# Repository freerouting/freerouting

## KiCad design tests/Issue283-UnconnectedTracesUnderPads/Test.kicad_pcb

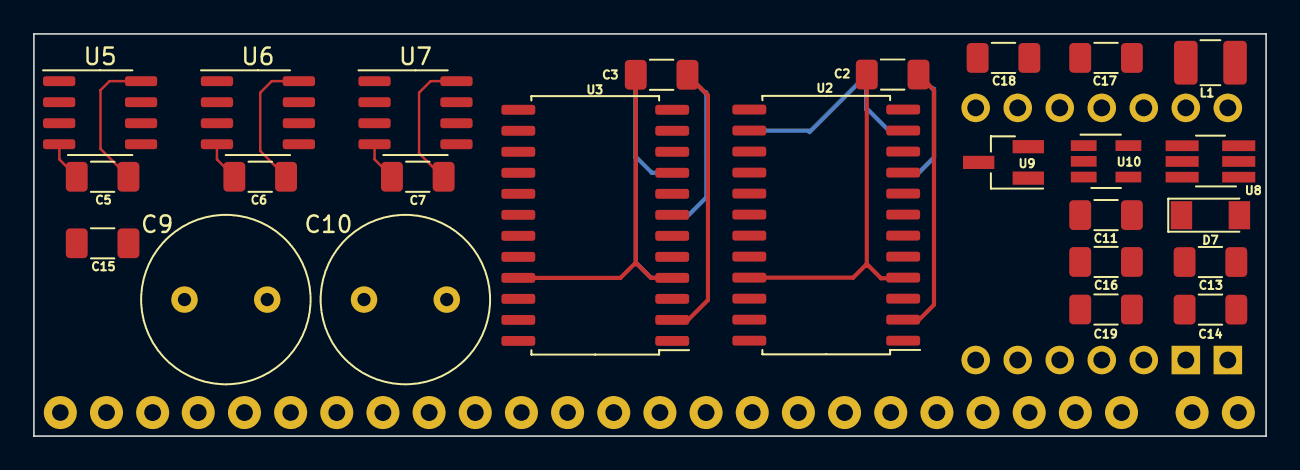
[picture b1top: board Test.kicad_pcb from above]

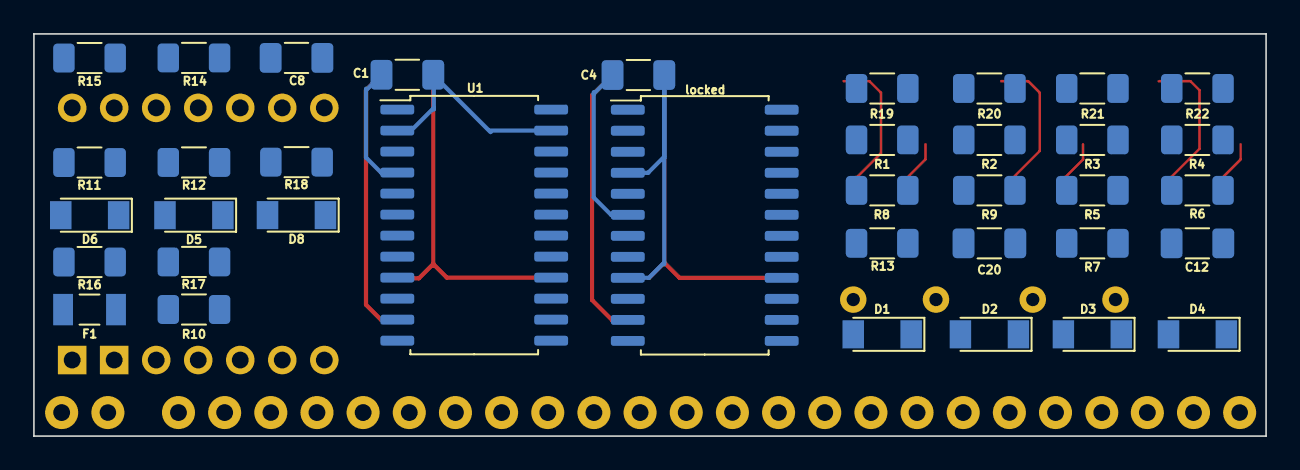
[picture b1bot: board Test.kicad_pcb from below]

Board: 2 copper layers, 74.5 x 24.3 mm, 89 parts (37 on the bottom side), 57 nets.

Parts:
C1, C2, C3, C4, C5, C6, C7, C8, C12, C19: 0.1u; C_1206_3216Metric_Pad1.33x1.80mm_HandSolder
C9, C10: 47u; C_Radial_D10.0mm_H12.5mm_P5.00mm
C11: 10u; C_1206_3216Metric_Pad1.33x1.80mm_HandSolder
C13, C14, C15: 47u; C_1206_3216Metric_Pad1.33x1.80mm_HandSolder
C16, C17, C18, C20: 0.01u; C_1206_3216Metric_Pad1.33x1.80mm_HandSolder
D1, D2, D3, D4, D5, D6, D7, D8: LL4148; D_MiniMELF
F1: 0.1 A; Fuse_Bussman_1206_3216Metric_Pad1.42x1.75mm_HandSolder
J1: 1A+; SolderWirePad_1x01_Drill0.8mm
J2: 1A-; SolderWirePad_1x01_Drill0.8mm
J3: 1B+; SolderWirePad_1x01_Drill0.8mm
J4: 1B-; SolderWirePad_1x01_Drill0.8mm
J5: 2A+; SolderWirePad_1x01_Drill0.8mm
J6: 2A-; SolderWirePad_1x01_Drill0.8mm
J7: 2B+; SolderWirePad_1x01_Drill0.8mm
J8: 2B-; SolderWirePad_1x01_Drill0.8mm
J9: 3A+; SolderWirePad_1x01_Drill0.8mm
J10: 3A-; SolderWirePad_1x01_Drill0.8mm
J11: 3B+; SolderWirePad_1x01_Drill0.8mm
J12: 3B-; SolderWirePad_1x01_Drill0.8mm
J13: POT A; SolderWirePad_1x01_Drill0.8mm
J14: POT B; SolderWirePad_1x01_Drill0.8mm
J15: VOL W; SolderWirePad_1x01_Drill0.8mm
J16: PRE W; SolderWirePad_1x01_Drill0.8mm
J17: MOD W; SolderWirePad_1x01_Drill0.8mm
J18: LED +; SolderWirePad_1x01_Drill0.8mm
J19: LED D; SolderWirePad_1x01_Drill0.8mm
J20: LED -; SolderWirePad_1x01_Drill0.8mm
J21: OUT +; SolderWirePad_1x01_Drill0.8mm
J22: OUT -; SolderWirePad_1x01_Drill0.8mm
J23: OUT G; SolderWirePad_1x01_Drill0.8mm
J24: BAT +; SolderWirePad_1x01_Drill0.8mm
J25: BAT -; SolderWirePad_1x01_Drill0.8mm
J28: GND; SolderWirePad_1x01_Drill0.8mm
L1: 4.7u; L_1210_3225Metric_Pad1.42x2.65mm_HandSolder
R1, R2, R3, R4, R14: 1M; R_1206_3216Metric_Pad1.30x1.75mm_HandSolder
R5, R6: 47k; R_1206_3216Metric_Pad1.30x1.75mm_HandSolder
R7: 10; R_1206_3216Metric_Pad1.30x1.75mm_HandSolder
R8, R9: 100; R_1206_3216Metric_Pad1.30x1.75mm_HandSolder
R10, R13: 1K; R_1206_3216Metric_Pad1.30x1.75mm_HandSolder
R11, R12: 100k; R_1206_3216Metric_Pad1.30x1.75mm_HandSolder
R15: 10M; R_1206_3216Metric_Pad1.30x1.75mm_HandSolder
R16: 300k; R_1206_3216Metric_Pad1.30x1.75mm_HandSolder
R17: 10k; R_1206_3216Metric_Pad1.30x1.75mm_HandSolder
R18: 43k; R_1206_3216Metric_Pad1.30x1.75mm_HandSolder
R19, R20, R21, R22: 4k7; R_1206_3216Metric_Pad1.30x1.75mm_HandSolder
U1, U2, U3: MAX395CWG+; SOIC-24W_7.5x15.4mm_P1.27mm
U5, U6, U7: OPA2314/OPA2205/OPA1692; SOIC-8_3.9x4.9mm_P1.27mm
U8: AP63205WU; TSOT-23-6_HandSoldering
U9: ATL431; SOT-23_Handsoldering
U10: AP7383-44WR-7; SOT-23-5_HandSoldering
U11: SeeeduinoXIAO; Seeeduino_XIAO-MOUDLE14P-2.54-21X17.8MM_PINS
locked: AD5206BRZ50; SOIC-24W_7.5x15.4mm_P1.27mm

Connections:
+5V: C1.1, C2.1, C3.1, C4.1, C5.1, C6.1, C7.1, C13.1, C14.1, D1.1 (K), D2.1 (K), D7.2 (A), J18.1, L1.2, R11.1, U1.2 (V+), U1.23 (*RESET), U2.2 (V+), U2.23 (*RESET), U3.2 (V+), U3.23 (*RESET), U5.8 (V+), U6.8 (V+), U7.8 (V+), U8.1 (FB), locked.6 (VDD)
GND: C1.2, C2.2, C3.2, C4.2, C5.2, C6.2, C7.2, C11.2, C12.1, C13.2, C14.2, C15.2, C16.2, C17.2, C18.2, C19.2, D3.2 (A), D4.2 (A), D6.2 (A), J14.1, J20.1, J25.1, J28.1, R7.1, R12.2, R14.2, R18.2, U1.4 (GND), U1.21 (V-), U2.4 (GND), U2.21 (V-), U3.4 (GND), U3.21 (V-), U5.4 (V-), U6.4 (V-), U7.4 (V-), U8.4 (GND), U9.3 (A), U10.1 (GND), U11.13 (GND), locked.4 (GND), locked.9 (VSS)
unnamed: C8.1, U8.6 (BST)
unnamed: C8.2, L1.1, U8.5 (SW)
unnamed: C9.2, R8.1
unnamed: C10.1, D2.2 (A), D4.1 (K), R5.1, U5.7 (OUTB)
unnamed: C10.2, R9.1
unnamed: C11.1, D5.1 (K), D6.1 (K), F1.1, R15.2, U8.3 (IN), U10.2 (VIN)
unnamed: C12.2, J23.1, R7.2
unnamed: C15.1, J2.1, R1.1, R2.1, R3.2, R4.2, R11.2, R12.1, U1.16 (NO5), U1.20 (NO7), U2.7 (NO1), U2.11 (NO3), U2.16 (NO5), U2.20 (NO7), U3.7 (NO1), U3.11 (NO3), U3.16 (NO5), U3.20 (NO7), U5.3 (+INA), U5.5 (+INB), locked.13 (B3), locked.16 (B1), locked.21 (B2), locked.24 (B4)
unnamed: C16.1, J16.1, U11.2 (PA4_A1_D1)
unnamed: C17.1, J15.1, U11.1 (PA02_A0_D0)
unnamed: C18.1, J17.1, U11.7 (PB08_A6_D6_TX)
unnamed: C19.1, R14.1, R15.1, U11.3 (PA10_A2_D2)
unnamed: C9.1, C20.1, D1.2 (A), D3.1 (K), R6.2, U5.1 (OUTA), locked.1 (A6), locked.2 (W6), locked.12 (A5)
unnamed: C20.2, locked.11 (W5)
unnamed: D5.2 (A), R10.2, R13.1, R16.1, U9.1 (K)
unnamed: D7.1 (K), D8.1 (K), U11.14 (5V)
unnamed: D8.2 (A), U10.3 (VOUT)
unnamed: F1.2, J24.1
unnamed: J1.1, R1.2, U1.6 (COM0), U6.3 (+INA)
unnamed: J3.1, U1.13 (COM4), U1.15 (COM5)
unnamed: J4.1, U1.17 (COM6), U1.19 (COM7)
unnamed: J5.1, U2.6 (COM0), U2.8 (COM1)
unnamed: J6.1, U1.10 (COM2), U2.10 (COM2), U2.12 (COM3)
unnamed: J7.1, U1.9 (NO2), U2.13 (COM4), U2.15 (COM5)
unnamed: J8.1, U2.17 (COM6), U2.19 (COM7)
unnamed: J9.1, U3.6 (COM0), U3.8 (COM1)
unnamed: J10.1, U1.12 (COM3), U3.10 (COM2), U3.12 (COM3)
unnamed: J11.1, U1.11 (NO3), U3.13 (COM4), U3.15 (COM5)
unnamed: J12.1, U3.17 (COM6), U3.19 (COM7)
unnamed: J13.1, U11.10 (PA5_A9_D9_MISO), U11.12 (3V3)
unnamed: J19.1, U11.8 (PB09_A7_D7_RX)
unnamed: J21.1, R9.2, R13.2
unnamed: J22.1, R8.2, R10.1
unnamed: R2.2, U1.7 (NO1), U2.5 (NO0), U2.9 (NO2), U2.14 (NO4), U2.18 (NO6), U7.3 (+INA)
unnamed: R3.1, U1.5 (NO0), U1.8 (COM1), U1.14 (NO4), U1.18 (NO6), U6.5 (+INB)
unnamed: R4.1, U3.5 (NO0), U3.9 (NO2), U3.14 (NO4), U3.18 (NO6), U7.5 (+INB)
unnamed: R5.2, R6.1, U5.6 (-INB)
unnamed: R16.2, R17.1
unnamed: R17.2, R18.1, U9.2 (REF)
unnamed: R19.1, locked.17 (W1)
unnamed: R19.2, R20.2, R21.2, R22.2, U5.2 (-INA), locked.3 (B6), locked.10 (B5)
unnamed: R20.1, locked.20 (W2)
unnamed: R21.1, locked.14 (W3)
unnamed: R22.1, locked.23 (W4)
unnamed: U1.1 (SCLK), U2.1 (SCLK), U3.1 (SCLK), U11.9 (PA7_A8_D8_SCK), locked.8 (CLK)
unnamed: U1.3 (DIN), U11.11 (PA6_A10_D10_MOSI), locked.7 (SDI)
unnamed: U1.22 (DOUT), U2.3 (DIN)
unnamed: U1.24 (*CS), U2.24 (*CS), U3.24 (*CS), U11.5 (PA8_A4_D4_SDA)
unnamed: U2.22 (DOUT), U3.3 (DIN)
unnamed: U7.1 (OUTA), U7.2 (-INA), locked.15 (A3)
unnamed: U6.1 (OUTA), U6.2 (-INA), locked.18 (A1)
unnamed: U6.6 (-INB), U6.7 (OUTB), locked.19 (A2)
unnamed: U7.6 (-INB), U7.7 (OUTB), locked.22 (A4)
unnamed: U8.2 (EN), U11.4 (PA11_A3_D3)
unnamed: U11.6 (PA9_A5_D5_SCL), locked.5 (CS*)

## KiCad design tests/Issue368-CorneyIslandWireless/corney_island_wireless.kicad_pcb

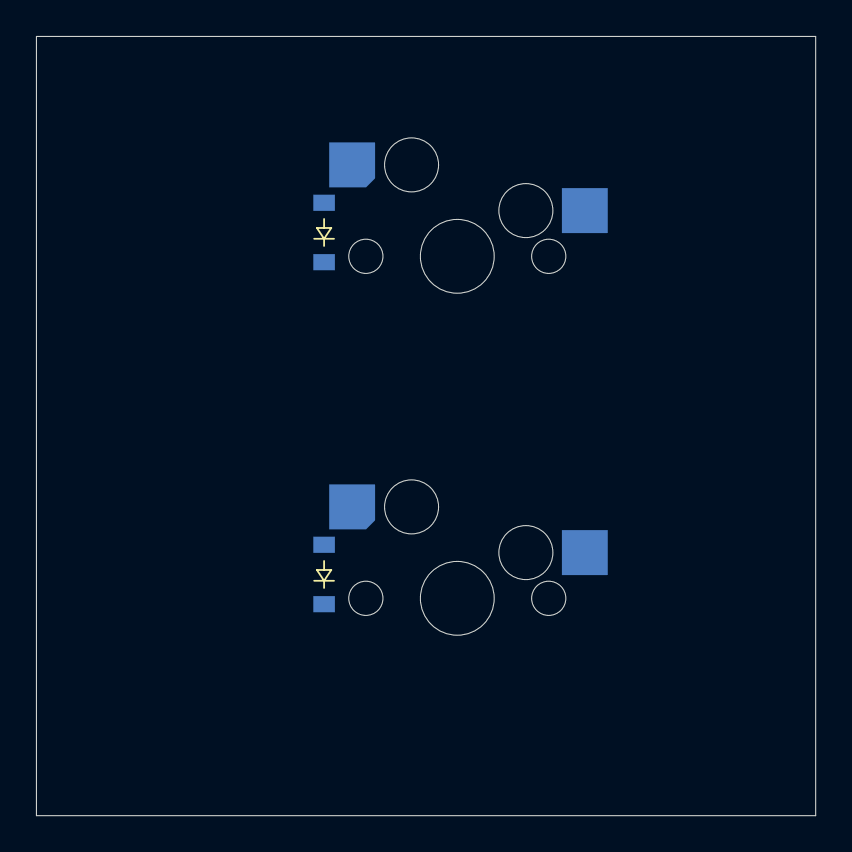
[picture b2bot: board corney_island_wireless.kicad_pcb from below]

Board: 2 copper layers, 43.3 x 43.3 mm, 4 parts (4 on the bottom side), 3 nets, no tracks yet.

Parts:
D16, D17: diode_tht_sod123
S16, S17: switch_mx

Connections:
C5: S16.1, S17.1
inner_bottom_B: D16.2, S16.2
inner_home_B: D17.2, S17.2

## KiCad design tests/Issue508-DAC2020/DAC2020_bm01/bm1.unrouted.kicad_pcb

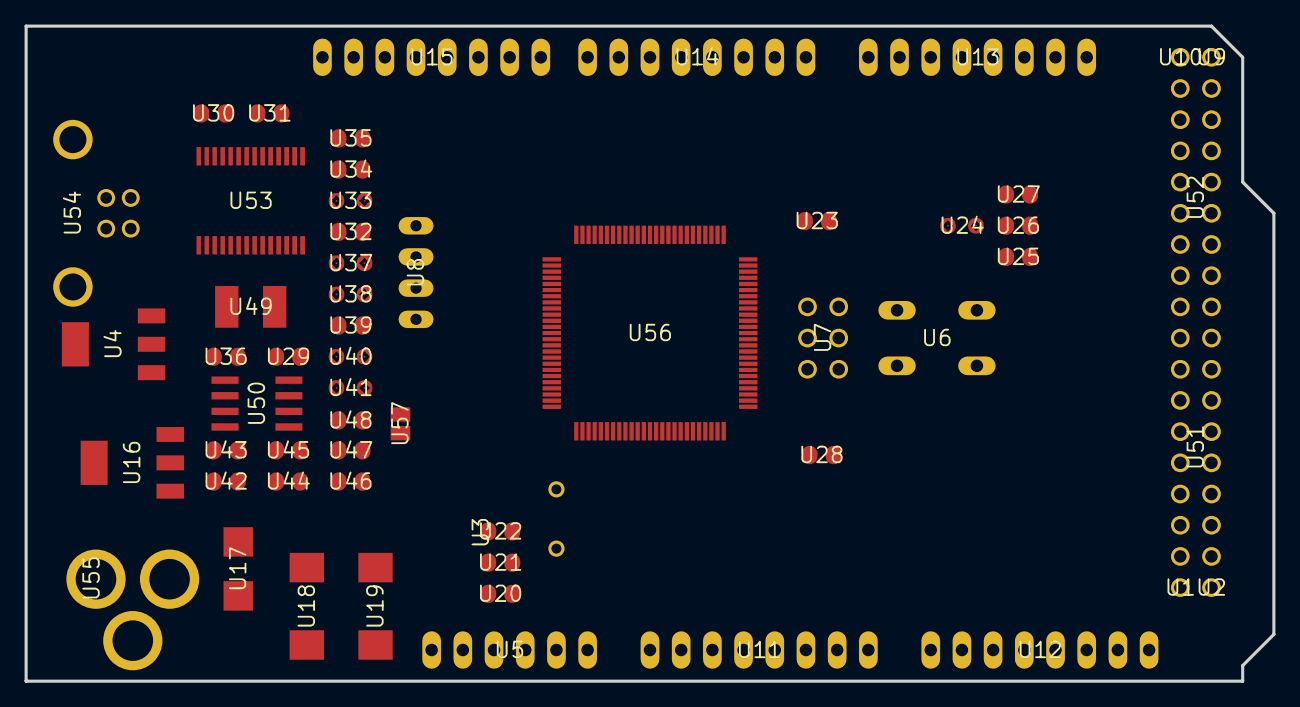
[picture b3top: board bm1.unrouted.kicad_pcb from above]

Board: 2 copper layers, 101.6 x 53.3 mm, 57 parts (0 on the bottom side), 99 nets, no tracks yet.

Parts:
U1, U2, U9, U10: 1X01
U3: HC49_S
U4, U16: SOT223
U5: 1X06
U6: B3F-10XX
U7: 2X03
U8: JP4
U11, U12, U13, U14, U15: 1X08
U17: SMB
U18, U19: SMC_D
U20, U21, U22, U23, U28, U29, U30, U31, U35, U36, U43, U44, U46, U48: C0805RND
U24, U33, U37, U38: 0805RND
U25, U26, U27, U32, U34, U39, U42, U45, U47: R0805RND
U40, U41: RCL_0805RND
U49: L1812
U50: SO08
U51, U52: 2X08
U53: SSOP28
U54: PN61729
U55: DC-21MM
U56: TQFP100
U57: SJ

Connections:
+3V3: U5.2, U30.2, U50.2, U53.17
+5V: U4.3, U5.3, U7.2, U9.1, U10.1, U16.2, U16.4, U19.+, U20.1, U23.1, U25.1, U26.1, U27.1, U28.1, U29.2, U31.1, U32.2, U39.2, U47.2, U50.8, U53.4, U53.19, U53.20, U56.10, U56.31, U56.61, U56.80, U56.100
ADC0: U11.1, U56.97
ADC1: U11.2, U56.96
ADC2: U11.3, U56.95
ADC3: U11.4, U56.94
ADC4: U11.5, U56.93
ADC5: U11.6, U56.92
ADC6: U11.7, U56.91
ADC7: U11.8, U56.90
ADC8: U12.1, U56.89
ADC9: U12.2, U56.88
ADC10: U12.3, U56.87
ADC11: U12.4, U56.86
ADC12: U12.5, U56.85
ADC13: U12.6, U56.84
ADC14: U12.7, U56.83
ADC15: U12.8, U56.82
AREF: U15.8, U35.1, U56.98
CMP: U42.1, U44.2, U45.2, U50.3
CTS: U8.1, U53.11
D+: U53.15, U54.3
D-: U53.16, U54.2
DCD: U8.3, U53.10
DSR: U8.2, U53.9
DTR: U48.1, U53.2, U57.1, U57.2
GATE_CMD: U4.1, U50.6, U50.7
GND: U1.1, U2.1, U5.4, U5.5, U6.1, U6.2, U7.6, U15.7, U16.1, U18.-, U19.-, U20.2, U21.1, U22.1, U23.2, U24.P$2, U28.2, U29.1, U30.1, U31.2, U33.P$2, U35.2, U36.2, U43.2, U44.1, U45.1, U46.2, U50.4, U53.7, U53.18, U53.21, U53.25, U53.26, U54.4, U54.P$1, U54.P$2, U55.1, U55.3, U56.11, U56.32, U56.62, U56.81, U56.99
M8RXD: U40.P$1, U53.1
M8TXD: U41.P$1, U53.5
unnamed: U33.P$1, U34.2
unnamed: U24.P$1, U25.2
unnamed: U50.1, U50.5
unnamed: U3.1, U21.2, U56.34
unnamed: U3.2, U22.2, U56.33
unnamed: U38.P$2, U53.23
unnamed: U37.P$2, U53.22
unnamed: U32.1, U38.P$1
unnamed: U37.P$1, U39.1
unnamed: U49.2, U54.1
PA0: U52.16, U56.78
PA1: U52.15, U56.77
PA2: U52.14, U56.76
PA3: U52.13, U56.75
PA4: U52.12, U56.74
PA5: U52.11, U56.73
PA6: U52.10, U56.72
PA7: U52.9, U56.71
PB0: U51.1, U56.19
PB1: U7.3, U51.2, U56.20
PB2: U7.4, U51.3, U56.21
PB3: U7.1, U51.4, U56.22
PB4: U15.3, U56.23
PB5: U15.4, U56.24
PB6: U15.5, U56.25
PB7: U15.6, U34.1, U56.26
PC0: U52.1, U56.53
PC1: U52.2, U56.54
PC2: U52.3, U56.55
PC3: U52.4, U56.56
PC4: U52.5, U56.57
PC5: U52.6, U56.58
PC6: U52.7, U56.59
PC7: U52.8, U56.60
PD7: U51.16, U56.50
PE0: U14.1, U40.P$2, U56.2
PE1: U14.2, U41.P$2, U56.3
PE3: U14.6, U56.5
PE4: U14.3, U56.6
PE5: U14.4, U56.7
PG0: U51.13, U56.51
PG1: U51.14, U56.52
PG2: U51.15, U56.70
PG5: U14.5, U56.1
PH3: U14.7, U56.15
PH4: U14.8, U56.16
PH5: U15.1, U56.17
PH6: U15.2, U56.18
PL0: U51.5, U56.35
PL1: U51.6, U56.36
PL2: U51.7, U56.37
PL3: U51.8, U56.38
PL4: U51.9, U56.39
PL5: U51.10, U56.40
PL6: U51.11, U56.41
PL7: U51.12, U56.42
PWRIN: U17.A, U55.2
RESET: U5.1, U6.3, U6.4, U7.5, U46.1, U47.1, U48.2, U56.30
RI: U8.4, U53.6
RXD1: U13.3, U56.45
RXD2: U13.5, U56.12
RXD3: U13.7, U56.63
SCL: U13.1, U26.2, U56.43
SDA: U13.2, U27.2, U56.44
TXD1: U13.4, U56.46
TXD2: U13.6, U56.13
TXD3: U13.8, U56.64
USBVCC: U4.2, U36.1, U49.1
VIN: U5.6, U16.3, U17.C, U18.+, U42.2, U43.1

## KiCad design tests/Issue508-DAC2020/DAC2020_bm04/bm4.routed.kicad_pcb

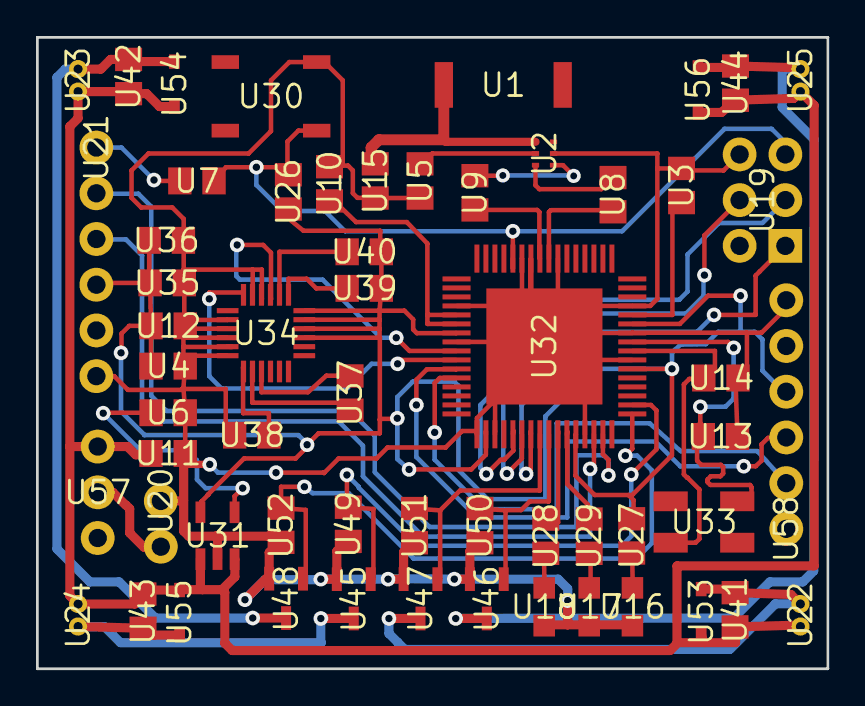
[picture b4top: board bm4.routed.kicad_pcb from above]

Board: 16 copper layers, 43.9 x 35.1 mm, 58 parts (0 on the bottom side), 44 nets.

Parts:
U1: ANTENNA-CHIP5
U2: BALUN-0805
U3, U4, U5, U6, U7, U8, U9, U10, U11, U12, U13, U14, U15, U35, U36, U37, U38, U41, U42, U43, U44: C0805
U16, U17, U18: CHIP-LED0805
U19: 2X3-NS
U20: 1X02
U21, U58: FTDI_BASIC
U22, U23, U24, U25: 653002114822
U26, U27, U28, U29, U39, U40, U49, U50, U51, U52: R0805
U30: TACTILE_SWITCH_SMD
U31: SOT23-DBV
U32: QFN-64
U33: CRYSTAL-SMD-5X3
U34: LGA-24
U45, U46, U47, U48: CONTROLLER_SOT95P237X112-3N
U53, U54, U55, U56: SOD323_ST
U57: SWITCH-SPDT

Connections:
3.3V: U4.1, U12.1, U21.VCC, U26.2, U27.2, U31.5, U32.23, U32.34, U32.44, U32.54, U32.59, U34.15, U34.16, U34.17, U34.18, U35.1, U36.1, U39.2, U40.2, U58.VCC
/MISO: U19.1, U32.39
/MOSI: U19.4, U32.38
/PB4: U32.40, U47.1, U51.1
/PB5: U32.41, U46.1, U50.1
/PB6: U28.2, U32.42
/PB7: U29.2, U32.43
/PE3: U32.49, U48.1, U52.1
/PE4: U32.50, U45.1, U49.1
/RESET: U7.2, U19.5, U26.1, U30.1, U32.12
/RFANT: U1.FEED, U2.1, U15.2
/RX0: U21.TXO, U32.46
/RX1: U32.27, U58.TXO
/SCK: U19.3, U32.37
/SCL: U32.25, U34.21
/SDA: U32.26, U34.24
/TX0: U21.RXI, U32.47
/TX1: U32.28, U58.RXI
/VBAT: U11.1, U22.1, U23.1, U24.1, U25.1, U31.1, U31.3, U41.1, U42.1, U43.1, U44.1, U53.C, U54.C, U55.C, U56.C, U57.3
GND: U2.5, U3.2, U4.2, U5.2, U6.2, U10.2, U11.2, U12.2, U13.2, U14.2, U15.1, U16.C, U17.C, U18.C, U19.6, U20.1, U21.GND, U30.3, U31.2, U32.7, U32.10, U32.11, U32.20, U32.24, U32.33, U32.35, U32.45, U32.55, U32.58, U32.61, U32.65, U34.2, U34.3, U34.4, U34.5, U34.6, U34.22, U34.23, U35.2, U36.2, U38.1, U45.2, U46.2, U47.2, U48.2, U49.2, U50.2, U51.2, U52.2, U58.GND
unnamed: U18.A, U28.1
unnamed: U2.2, U5.1
unnamed: U2.3, U8.2
unnamed: U2.4, U9.1
unnamed: U17.A, U29.1
unnamed: U3.1, U32.60
unnamed: U10.1, U32.21, U32.22
unnamed: U13.1, U32.57, U33.3
unnamed: U14.1, U32.56, U33.1
unnamed: U22.2, U41.2, U47.3, U53.A
unnamed: U23.2, U42.2, U48.3, U54.A
unnamed: U6.1, U31.4
unnamed: U24.2, U43.2, U45.3, U55.A
unnamed: U25.2, U44.2, U46.3, U56.A
unnamed: U7.1, U21.DTR
unnamed: U8.1, U32.8
unnamed: U9.2, U32.9
unnamed: U34.9, U37.1
unnamed: U34.8, U37.2
unnamed: U34.7, U38.2
unnamed: U20.2, U57.2
unnamed: U16.A, U27.1
unnamed: U34.19, U39.1
unnamed: U34.20, U40.1

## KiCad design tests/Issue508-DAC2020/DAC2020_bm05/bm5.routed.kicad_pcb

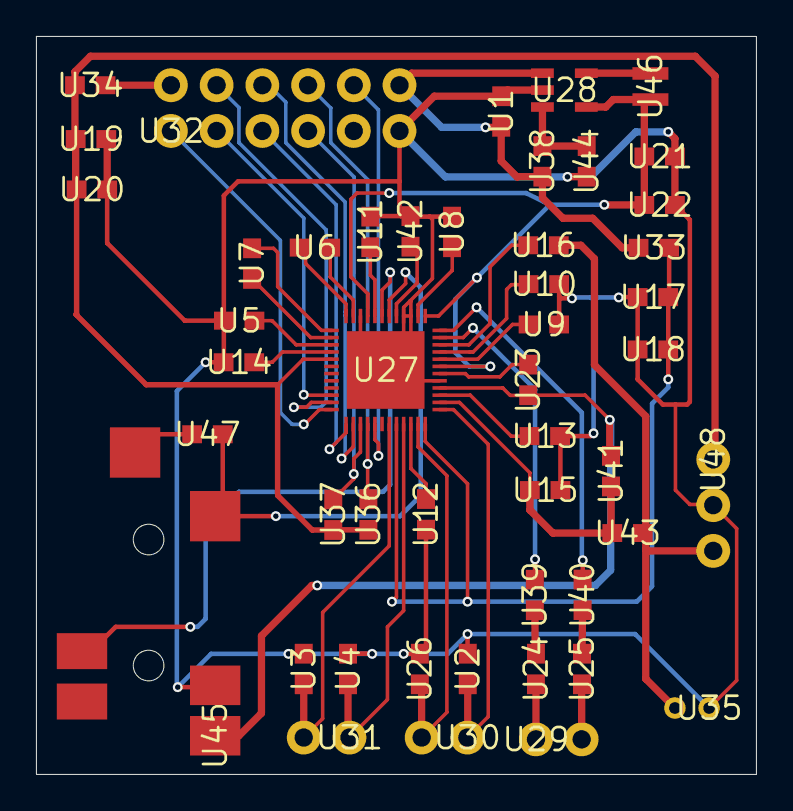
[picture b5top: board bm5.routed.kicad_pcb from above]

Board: 2 copper layers, 40.0 x 41.0 mm, 48 parts (0 on the bottom side), 47 nets.

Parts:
U1, U2, U3, U4, U5, U6, U7, U8, U9, U10, U11, U12, U13, U14, U15, U16, U17, U18, U19, U20, U21, U22, U23, U24, U25, U26, U33, U34, U36, U37, U38, U39, U40, U41, U42, U43, U44, U47: 0603
U27: QFN50P700X700X100-49N
U28: SOT95P284X122-5N
U29, U30, U31: 1X02
U32: 2X6
U35: CMC-2242PBL-A
U45: SJ-43514-SMT-TR
U46: NRH2412T2R2MNGH
U48: 1X03

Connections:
3.3V: U32.2, U34.2
5V: U1.2, U28.1, U32.12, U33.2, U38.1
/1.8VDD: U21.1, U22.1, U27.7, U27.13, U27.21, U28.4, U46.2
/3.3VDD: U19.1, U20.1, U27.29, U34.1, U36.1, U37.1, U48.1
/CPVREF: U27.17, U42.1
/HPOL: U27.18, U45.2, U47.1
/HPOR: U27.19, U45.3
/IN1P: U23.1, U27.4, U41.2, U45.1
/IN2P: U16.1, U35.2, U43.2, U48.3
/LOUTL: U27.11, U39.1
/LOUTR: U27.12, U40.1
/MICBIAS1: U15.2, U27.2, U41.1, U43.1
/SPKVDD: U17.1, U18.1, U27.44, U27.48, U33.1
/SPOLN: U26.1, U27.47, U30.2
/SPOLP: U2.1, U27.1, U30.1
/SPORN: U3.1, U27.43, U31.2
/SPORP: U4.1, U27.45, U31.1
/XADUIO_I2S0_BCLK: U27.37, U32.5
/XADUIO_I2S0_LRCKL: U27.36, U32.1
/XADUIO_SCL: U27.39, U32.7, U37.2
/XAUDIO_I2S0_DIN: U27.35, U32.4
/XAUDIO_I2S0_DOUT: U27.34, U32.3
/XAUDIO_I2S0_MCLK: U27.38, U32.6
/XAUDIO_IRQ: U27.41, U32.10
/XAUDIO_SDA: U27.40, U32.8, U36.2
GND: U1.1, U2.2, U3.2, U4.2, U5.2, U8.1, U9.1, U10.1, U11.2, U12.1, U13.1, U14.1, U15.1, U17.2, U18.2, U19.2, U20.2, U21.2, U22.2, U26.2, U27.5, U27.15, U27.16, U27.22, U27.49, U28.2, U32.11, U35.1, U42.2, U44.1, U45.4, U48.2
unnamed: U11.1, U27.20
unnamed: U23.2, U27.6
unnamed: U24.1, U39.2
unnamed: U24.2, U29.1
unnamed: U25.1, U40.2
unnamed: U25.2, U29.2
unnamed: U5.1, U27.27
unnamed: U6.1, U27.24
unnamed: U6.2, U27.23
unnamed: U7.1, U27.25
unnamed: U7.2, U27.26
unnamed: U8.2, U27.14
unnamed: U9.2, U27.8
unnamed: U10.2, U27.9
unnamed: U12.2, U27.46
unnamed: U13.2, U27.3
unnamed: U14.2, U27.28
unnamed: U16.2, U27.10
unnamed: U28.3, U38.2, U44.2
unnamed: U28.5, U46.1
unnamed: U45.5, U47.2

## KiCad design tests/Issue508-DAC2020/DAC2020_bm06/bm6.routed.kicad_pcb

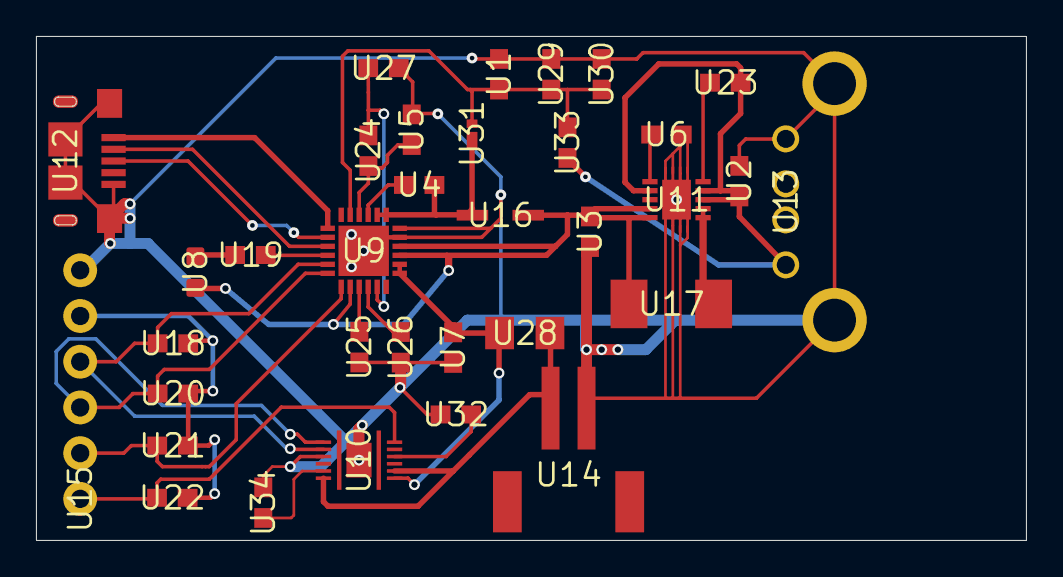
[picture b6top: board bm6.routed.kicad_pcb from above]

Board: 2 copper layers, 55.0 x 28.0 mm, 34 parts (0 on the bottom side), 27 nets.

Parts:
U1, U2, U3, U4, U5, U6, U7, U18, U19, U20, U21, U22, U23, U24, U25, U26, U27, U29, U30, U32, U33, U34: 0603
U8: LED-0603
U9: QFN50P400X400X100-25N
U10: BQ27441DRZRG1A
U11: SON50P300X300X100-11N
U12: 10118193-0001LF
U13: UE27AC54100
U14: JST-2-SMD
U15: 1X06
U16: INDPM3630X200N
U17: INDPM5552X200N
U28: 1206
U31: DSN2_1

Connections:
3.3V: U15.5, U18.2, U20.2, U21.2, U22.2
5V: U2.1, U11.3, U11.4, U11.7, U13.1, U23.1, U33.2
/CHG_INT: U9.7, U15.2, U21.1
/FUEL_INT: U10.12, U15.1, U22.1
/REG: U5.1, U9.22, U24.1
/SCL: U9.5, U10.2, U15.4, U18.1
/SDA: U9.6, U10.1, U15.3, U20.1
/VBAT_CELL: U7.1, U9.13, U9.14, U10.7, U28.1
/VBAT_MAIN: U3.1, U8.A, U9.8, U9.15, U9.16, U11.9, U11.10, U16.2, U17.1
GND: U1.2, U2.2, U3.2, U5.2, U6.2, U7.2, U9.17, U9.18, U9.25, U10.3, U10.13, U11.GND@1, U11.GND@2, U11.GND@3, U11.GND@4, U11.GND@5, U11.GND@6, U11.GND@7, U11.GND@8, U11.GND@9, U12.GND, U12.SHIELD$1, U12.SHIELD$2, U12.SHIELD$3, U12.SHIELD$4, U13.4, U13.5, U13.6, U14.1, U15.6, U25.1, U26.1, U27.1, U29.2, U30.2, U32.1, U34.2
unnamed: U4.1, U9.19, U9.20, U16.1, U31.2
unnamed: U4.2, U9.21
unnamed: U1.1, U9.23, U29.1, U30.1, U31.1, U33.1
unnamed: U6.1, U11.6
unnamed: U10.5, U34.1
unnamed: U8.C, U19.1
unnamed: U9.1, U12.VCC
unnamed: U9.2, U12.D+
unnamed: U9.3, U12.D-
unnamed: U9.4, U19.2
unnamed: U9.9, U25.2
unnamed: U9.10, U26.2
unnamed: U9.11, U24.2, U27.2
unnamed: U10.6, U10.8, U14.2, U28.2
unnamed: U10.10, U32.2
unnamed: U11.1, U11.2, U17.2
unnamed: U11.5, U23.2

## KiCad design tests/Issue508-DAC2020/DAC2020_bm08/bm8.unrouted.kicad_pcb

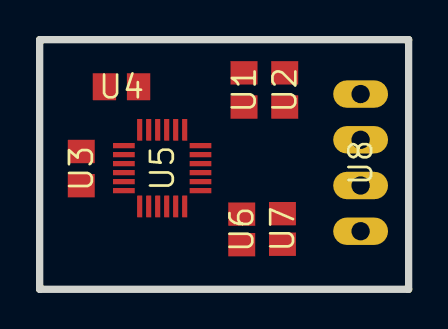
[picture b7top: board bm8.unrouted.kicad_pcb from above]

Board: 2 copper layers, 20.5 x 13.9 mm, 8 parts (0 on the bottom side), 9 nets, no tracks yet.

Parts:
U1, U2, U3, U4: C0805
U5: LGA-24
U6, U7: R0805
U8: MA04-1

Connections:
/SCL: U5.21, U8.2
/SDA: U5.24, U8.3
GND: U1.2, U2.2, U4.1, U5.2, U5.3, U5.4, U5.5, U5.6, U5.22, U5.23, U8.4
unnamed: U3.1, U5.9
unnamed: U3.2, U5.8
unnamed: U4.2, U5.7
unnamed: U5.19, U6.1
unnamed: U5.20, U7.1
VDD: U1.1, U2.1, U5.15, U5.16, U5.17, U5.18, U6.2, U7.2, U8.1
